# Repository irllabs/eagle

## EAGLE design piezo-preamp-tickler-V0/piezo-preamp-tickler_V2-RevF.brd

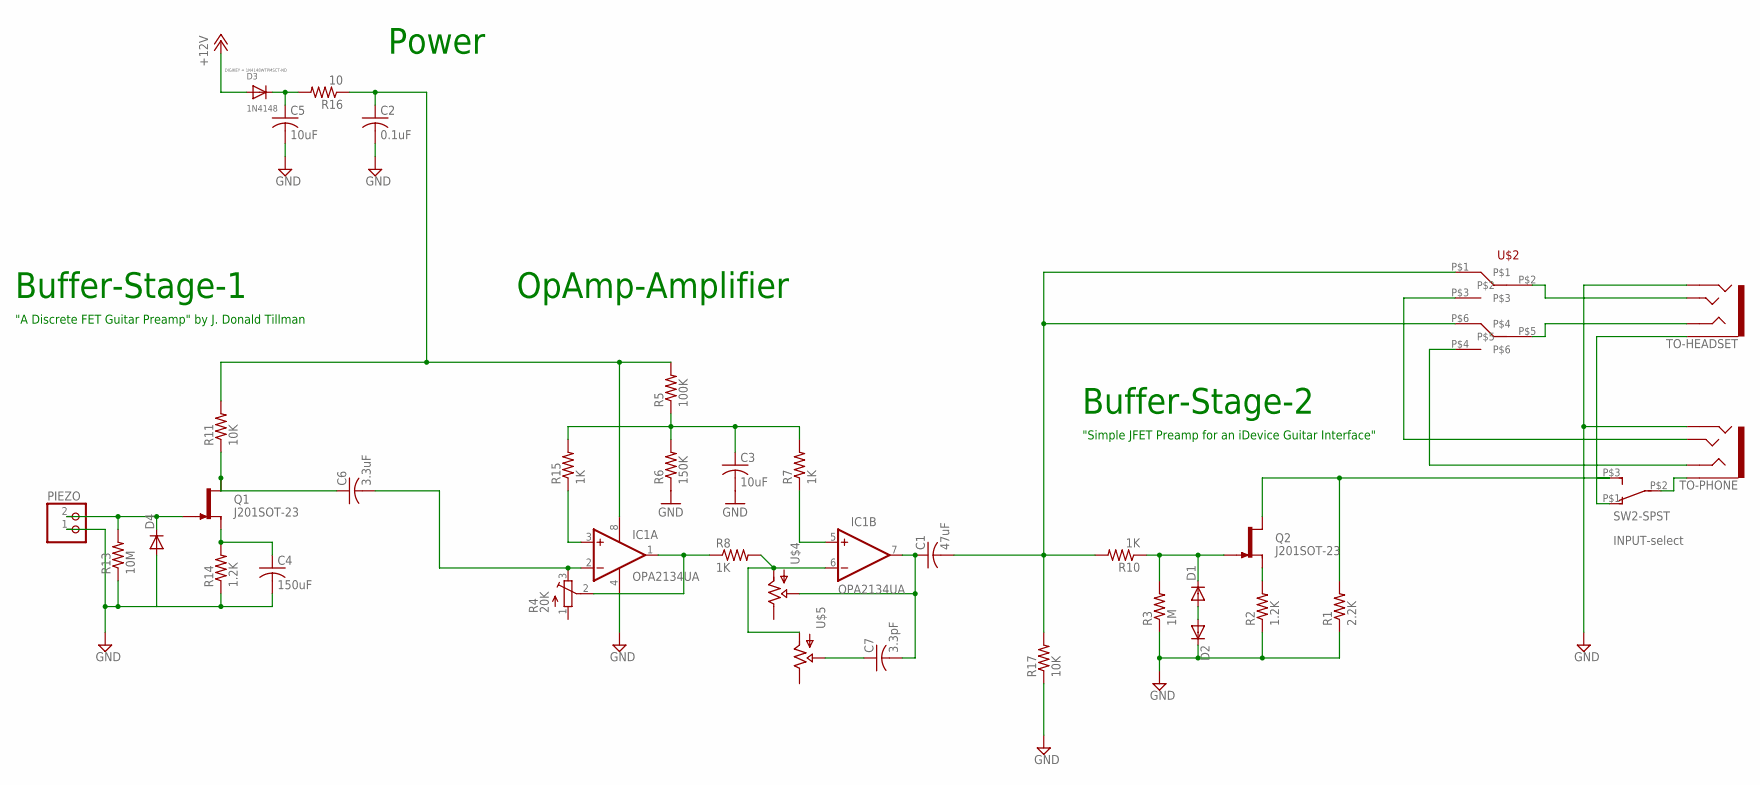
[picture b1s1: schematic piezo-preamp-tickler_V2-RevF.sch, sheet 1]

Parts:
C1: 47uF; CT7343
C2: 0.1uF; C0805K
C3, C5: 10uF; C0805K
C4: 150uF; CT7343
C6: 3.3uF; CT7343
C7: 3.3pF; C0805K
D1, D2, D4: DIODE-SOD123; SOD123
D3: 1N4148; SOD-123; DIGIKEY 1N4148WTPMSCT-ND
IC1: OPA2134UA; SO08
PIEZO: JST_2PIN-THM; JST-PH-2-THM
Q1, Q2: J201SOT-23; SOT23-3
R1: 2.2K; R0603
R2, R14: 1.2K; R0603
R3: 1M; R0603
R4: 20K; TC33X
R5: 100K; R0603
R6: 150K; R0603
R7, R8, R10, R15: 1K; R0603
R11, R17: 10K; R0603
R13: 10M; R0603
R16: 10; R0603
SW2-SPST: INPUT-select; SWITCH_SPDT_CL-SB-12B
TO-HEADSET: AUDIO-JACK3LGPADS; AUDIO-JACK-TRRS-SMD
TO-PHONE: AUDIO-JACK3LGPADS; AUDIO-JACK-TRRS-SMD
U$2: SWITCH_DPDT; SWITCH_DPDT_CL-SB-12B
U$4, U$5: POTTHUMBPOT14MM; THUMBPOT10MM

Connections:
+12V: D3.A; also elsewhere on the board
GND: C2.2, C3.2, C4.- (2), C5.2, D2.C, D4.A, IC1.4 (V-), PIEZO.1 (2), R1.1, R2.1, R3.1, R6.1, R13.1, R14.1, R17.1, TO-HEADSET.RING2, TO-PHONE.RING2; also elsewhere on the board
unnamed: D1.A, D2.A
unnamed: D4.C, PIEZO.2 (1), Q1.3 (G), R13.2
unnamed: Q2.2 (S), R2.2
unnamed: IC1.5 (+IN), R7.1
unnamed: C1.+ (1), C7.2, IC1.7 (OUT), U$4.P$2 (WIPER)
unnamed: IC1.6 (-IN), R8.2, U$4.P$1 (IN), U$5.P$1 (IN)
unnamed: C6.+ (1), Q1.1 (D), R11.1
unnamed: D1.C, Q2.3 (G), R3.2, R10.1
unnamed: C1.- (2), R10.2, R17.2, U$2.P$1, U$2.P$6
unnamed: SW2-SPST.P$1 (1), TO-HEADSET.EARTH
unnamed: TO-HEADSET.TIP, U$2.P$2
unnamed: C4.+ (1), Q1.2 (S), R14.2
unnamed: TO-HEADSET.RING1, U$2.P$5
unnamed: C5.1, D3.C, R16.2
unnamed: SW2-SPST.P$2 (2), TO-PHONE.EARTH
unnamed: IC1.3 (+IN), R15.1
unnamed: C3.1, R5.1, R6.2, R7.2, R15.2
unnamed: IC1.1 (OUT), R4.2 (S), R8.1
unnamed: C2.1, IC1.8 (V+), R5.2, R11.2, R16.1
unnamed: TO-PHONE.RING1, U$2.P$4
unnamed: TO-PHONE.TIP, U$2.P$3
unnamed: C6.- (2), IC1.2 (-IN), R4.3 (E)
unnamed: C7.1, U$5.P$2 (WIPER)
SELECT: Q2.1 (D), R1.2, SW2-SPST.P$3 (3)

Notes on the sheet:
Buffer-Stage-1
OpAmp-Amplifier
Buffer-Stage-2
"A Discrete FET Guitar Preamp" by J. Donald Tillman
"Simple JFET Preamp for an iDevice Guitar Interface"
Power

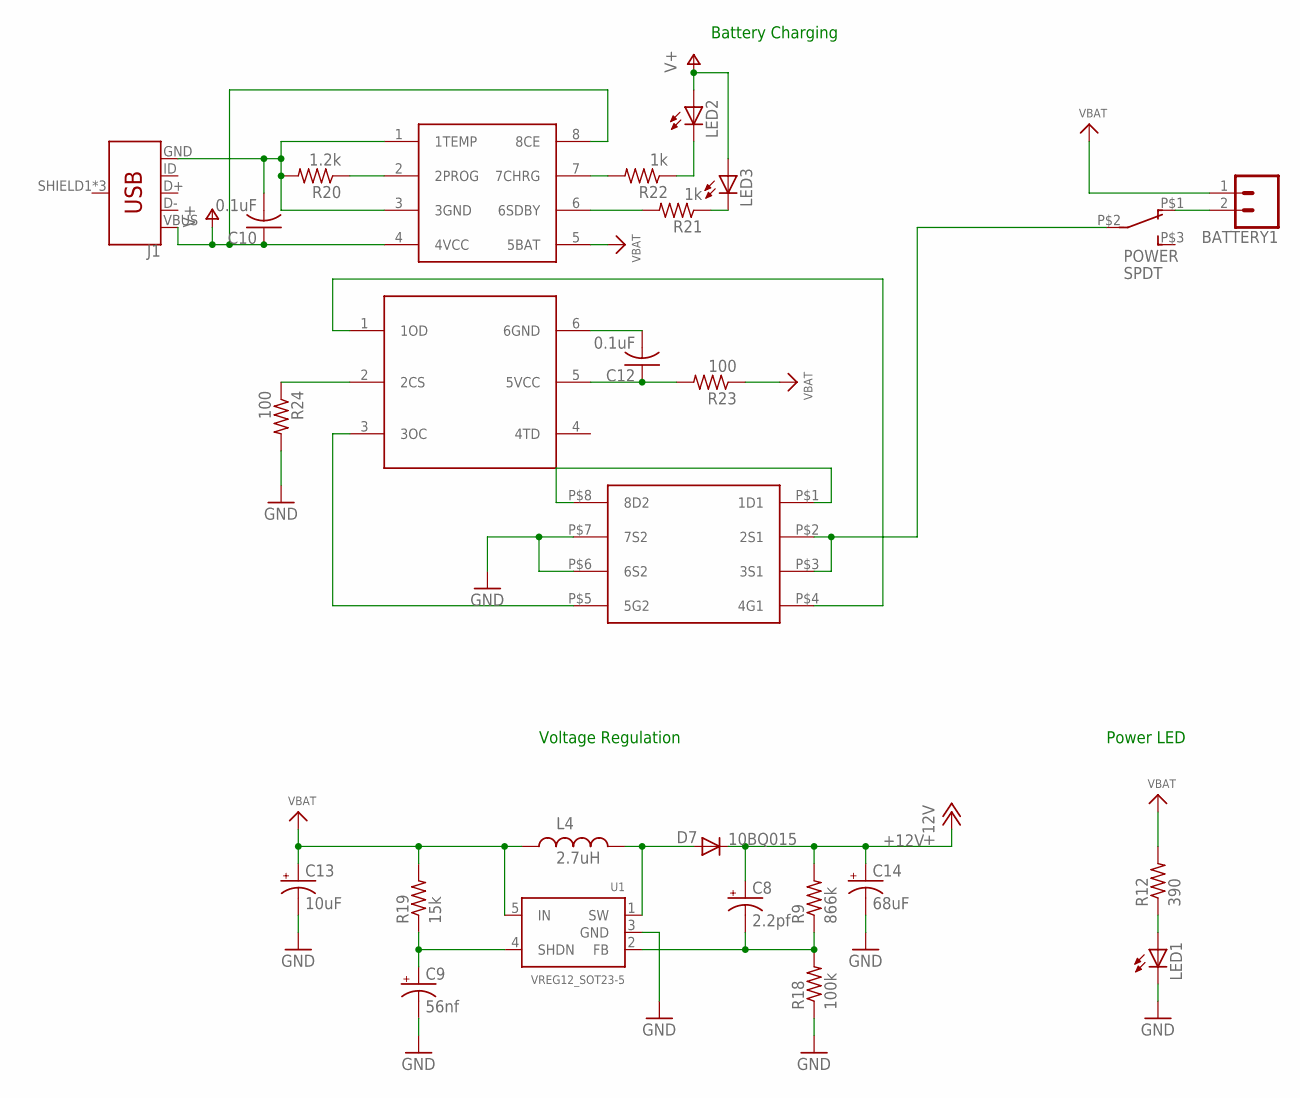
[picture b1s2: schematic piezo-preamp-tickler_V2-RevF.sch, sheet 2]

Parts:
BATTERY1: CONN_02LOCK; 1X02_LOCK
C8: 2.2pf; EIA3216
C9: 56nf; EIA3528
C10, C12: 0.1uF; C0805K
C13: 10uF; EIA3216
C14: 68uF; EIA3528
D7: 10BQ015; SMA-DIODE
J1: USB_MICRO-BREDUCED_PASTE; USB-B-MICRO-SMD_RED_PASTE
L4: 2.7uH; CR54
LED1, LED2, LED3: LED3MM
POWER: SPDT; SWITCH_SPDT_CL-SB-12B
R9: 866k; R0603
R12: 390; R0805
R18: 100k; R0603
R19: 15k; R0603
R20: 1.2k; R0603
R21, R22: 1k; R0603
R23, R24: 100; R0603
U1: VREG12_SOT23-5; SOT23-5
U$1: TP4056-CHIP; SO08
U$7: DW01A; SOT23-6
U$9: F8205A

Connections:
+12V: C8.A (+), C14.A (+), D7.C, R9.2; also elsewhere on the board
GND: C9.C (-), C13.C (-), C14.C (-), LED1.K (C), R18.1, R24.2, U1.3 (GND), U$9.P$6 (6S2), U$9.P$7 (7S2); also elsewhere on the board
unnamed: LED1.A, R12.1
unnamed: POWER.P$2 (2), U$9.P$2 (2S1), U$9.P$3 (3S1)
unnamed: BATTERY1.2, POWER.P$1 (1)
unnamed: C9.A (+), R19.1, U1.4 (SHDN)
unnamed: C8.C (-), R9.1, R18.2, U1.2 (FB)
unnamed: D7.A, L4.P$2 (2), U1.1 (SW)
unnamed: C10.2, J1.GND, R20.2, U$1.1 (1TEMP), U$1.3 (3GND)
unnamed: U$7.1 (1OD), U$9.P$4 (4G1)
unnamed: R20.1, U$1.2 (2PROG)
unnamed: U$7.3 (3OC), U$9.P$5 (5G2)
unnamed: R22.2, U$1.7 (7CHRG)
unnamed: R21.2, U$1.6 (6SDBY)
unnamed: LED3.K (C), R21.1
unnamed: LED2.K (C), R22.1
unnamed: C12.1, R23.2, U$7.5 (5VCC)
unnamed: C12.2, U$7.6 (6GND)
unnamed: R24.1, U$7.2 (2CS)
unnamed: U$9.P$1 (1D1), U$9.P$8 (8D2)
V+: C10.1, J1.VBUS, LED2.A, LED3.A, U$1.4 (4VCC), U$1.8 (8CE)
VBAT: BATTERY1.1, C13.A (+), L4.P$1 (1), R12.2, R19.2, R23.1, U1.5 (IN), U$1.5 (5BAT)

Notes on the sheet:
Voltage Regulation
Battery Charging
Power LED

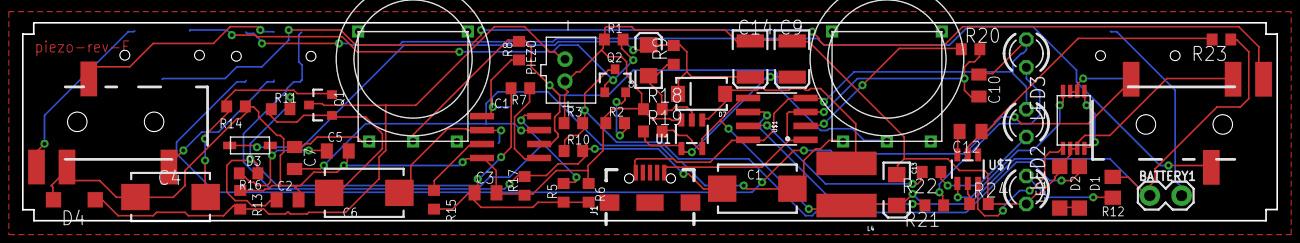
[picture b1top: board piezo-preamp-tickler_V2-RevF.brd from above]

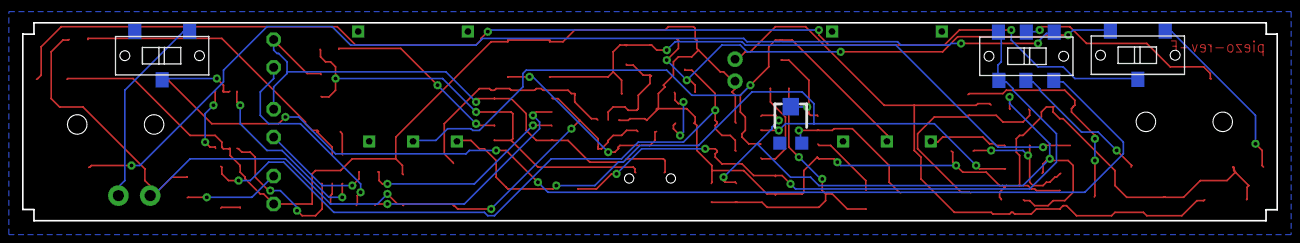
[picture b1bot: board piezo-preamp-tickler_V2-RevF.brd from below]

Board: 2 copper layers, 114.3 x 18.0 mm, 63 parts (4 on the bottom side), 46 nets.

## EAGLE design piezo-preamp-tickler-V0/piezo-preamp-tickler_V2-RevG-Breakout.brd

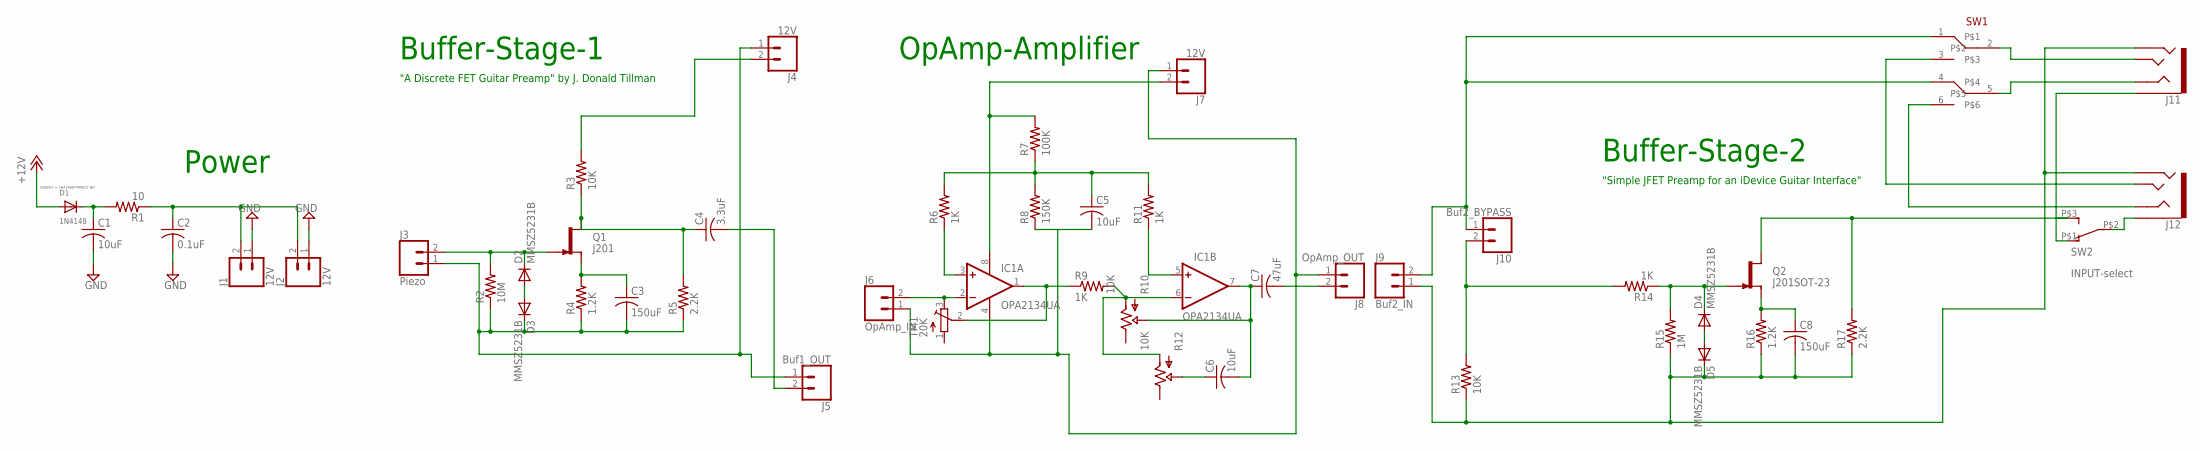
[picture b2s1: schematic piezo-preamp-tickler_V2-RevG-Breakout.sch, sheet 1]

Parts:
C1, C5, C6: 10uF; C0805K
C2: 0.1uF; C0805K
C3, C8: 150uF; CT7343
C4: 3.3uF; CT7343
C7: 47uF; CT7343
D1: 1N4148; SOD-123; DIGIKEY 1N4148WTPMSCT-ND
D2, D3, D4, D5: MMSZ5231B; SOD123
IC1: OPA2134UA; SO08
J1, J2, J4, J7: 12V; 1X02
J3: Piezo; 1X02
J5: Buf1_OUT; 1X02
J6: OpAmp_IN; 1X02
J8: OpAmp_OUT; 1X02
J9: Buf2_IN; 1X02
J10: Buf2_BYPASS; 1X02
J11, J12: AUDIO-JACK3LGPADS; AUDIO-JACK-TRRS-SMD
Q1: J201; SOT23-3
Q2: J201SOT-23; SOT23-3
R1: 10; R0805
R2: 10M; R0805
R3, R13: 10K; R0805
R4, R16: 1.2K; R0805
R5, R17: 2.2K; R0805
R6, R9, R11, R14: 1K; R0805
R7: 100K; R0805
R8: 150K; R0805
R10, R12: 10K; THUMBPOT14
R15: 1M; R0805
SW1: SWITCH_DPDT; SWITCH_DPDT_CL-SB-22B
SW2: INPUT-select; SWITCH_SPDT_CL-SB-12B
TM1: 20K; TC33X

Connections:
+12V: D1.A; also elsewhere on the board
GND: C1.2, C2.2, J1.1, J2.1; also elsewhere on the board
unnamed: D4.A, D5.A
unnamed: D2.C, J3.2, Q1.3 (G), R2.2
unnamed: C8.+ (1), Q2.2 (S), R16.2
unnamed: IC1.5 (+IN), R11.1
unnamed: C6.2, C7.+ (1), IC1.7 (OUT), R10.P$2 (WIPER)
unnamed: IC1.6 (-IN), R9.2, R10.P$1 (IN), R12.P$1 (IN)
unnamed: D2.A, D3.A
unnamed: C4.+ (1), Q1.1 (D), R3.1, R5.2
unnamed: D4.C, Q2.3 (G), R14.1, R15.2
unnamed: J9.2, J10.1, SW1.1, SW1.4
unnamed: J11.EARTH, SW2.P$1 (1)
unnamed: J11.TIP, SW1.2
unnamed: C3.+ (1), Q1.2 (S), R4.2
unnamed: J11.RING1, SW1.5
unnamed: C1.1, D1.C, R1.2
unnamed: J12.EARTH, SW2.P$2 (2)
unnamed: IC1.2 (-IN), J6.2, TM1.3 (E)
unnamed: C3.- (2), D3.C, J3.1, J4.1, J5.1, R2.1, R4.1, R5.1
unnamed: IC1.3 (+IN), R6.1
unnamed: C5.1, R6.2, R7.1, R8.2, R11.2
unnamed: IC1.1 (OUT), R9.1, TM1.2 (S)
unnamed: J4.2, R3.2
unnamed: J12.RING1, SW1.6
unnamed: J12.TIP, SW1.3
unnamed: C4.- (2), J5.2
unnamed: C6.1, R12.P$2 (WIPER)
unnamed: C7.- (2), J8.2
unnamed: IC1.8 (V+), J7.2, R7.2
unnamed: C2.1, J1.2, J2.2, R1.1
unnamed: C5.2, IC1.4 (V-), J6.1, J7.1, J8.1, R8.1
unnamed: C8.- (2), D5.C, J9.1, J11.RING2, J12.RING2, R13.1, R15.1, R16.1, R17.1
unnamed: J10.2, R13.2, R14.2
SELECT: Q2.1 (D), R17.2, SW2.P$3 (3)

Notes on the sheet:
Buffer-Stage-1
OpAmp-Amplifier
Buffer-Stage-2
"A Discrete FET Guitar Preamp" by J. Donald Tillman
"Simple JFET Preamp for an iDevice Guitar Interface"
Power

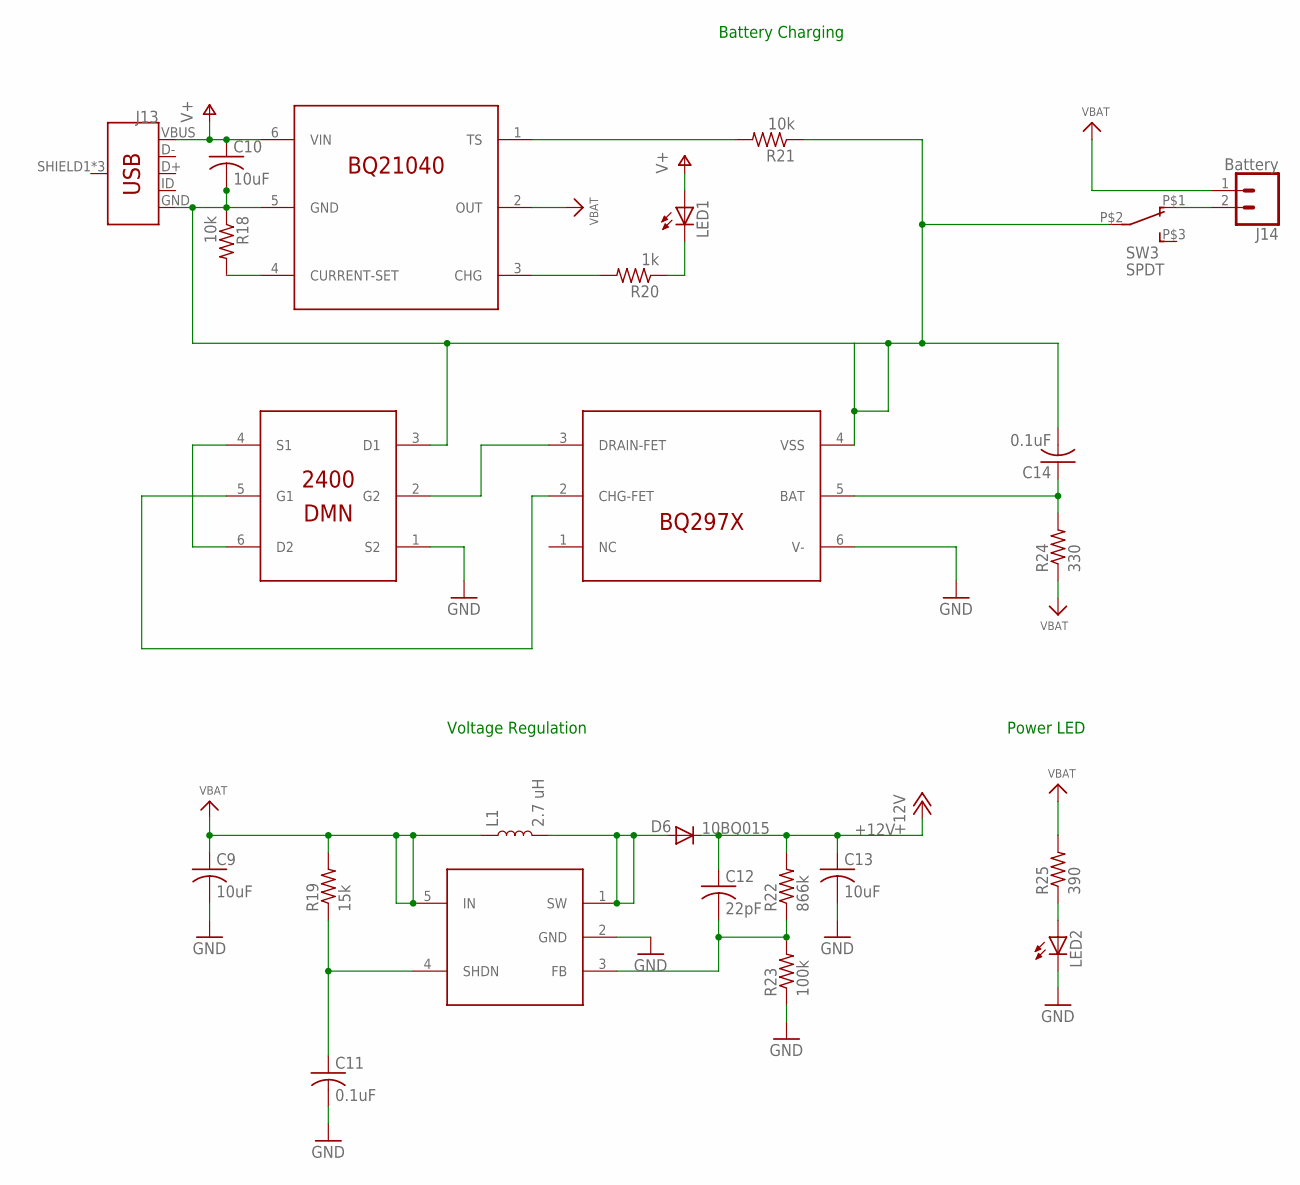
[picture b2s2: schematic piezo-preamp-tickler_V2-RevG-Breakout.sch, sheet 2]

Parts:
C9, C10, C13: 10uF; C0805K
C11, C14: 0.1uF; C0805K
C12: 22pF; C0805K
D6: 10BQ015; SMA-DIODE
J13: USB_MICRO-BREDUCED_PASTE; USB-B-MICRO-SMD_RED_PASTE
J14: Battery; 1X02_LOCK
L1: 2.7 uH; CR54
LED1, LED2: LED3MM
Q3: DMN2400; SOT-563
Q4: BQ21040; SOT23-6
Q5: SC4503; SOT23-5
Q6: BQ297X; WSON-6
R18, R21: 10k; R0805
R19: 15k; R0805
R20: 1k; R0805
R22: 866k; R0805
R23: 100k; R0805
R24: 330; R0805
R25: 390; R0805
SW3: SPDT; SWITCH_SPDT_CL-SB-12B

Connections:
+12V: C12.1, C13.1, D6.C, R22.2; also elsewhere on the board
GND: C9.2, C11.2, C13.2, LED2.K (C), Q3.1 (S2), Q5.2 (GND), Q6.6 (V-), R23.1; also elsewhere on the board
GND1: C10.2, C14.2, J13.GND, Q3.3 (D1), Q4.5 (GND), Q6.4 (VSS), R18.1, R21.1, SW3.P$2 (2)
unnamed: LED2.A, R25.1
unnamed: J14.2, SW3.P$1 (1)
unnamed: C11.1, Q5.4 (SHDN), R19.1
unnamed: C12.2, Q5.3 (FB), R22.1, R23.2
unnamed: D6.A, L1.P$2 (2), Q5.1 (SW)
unnamed: Q4.3 (CHG), R20.2
unnamed: C14.1, Q6.5 (BAT), R24.2
unnamed: Q4.1 (TS), R21.2
unnamed: Q3.4 (S1), Q3.6 (D2)
unnamed: Q4.4 (CURRENT-SET), R18.2
unnamed: Q3.5 (G1), Q6.2 (CHG-FET)
unnamed: LED1.K (C), R20.1
unnamed: Q3.2 (G2), Q6.3 (DRAIN-FET)
V+: C10.1, J13.VBUS, LED1.A, Q4.6 (VIN)
VBAT: C9.1, J14.1, L1.P$1 (1), Q4.2 (OUT), Q5.5 (IN), R19.2, R24.1, R25.2

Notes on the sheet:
Voltage Regulation
Battery Charging
Power LED

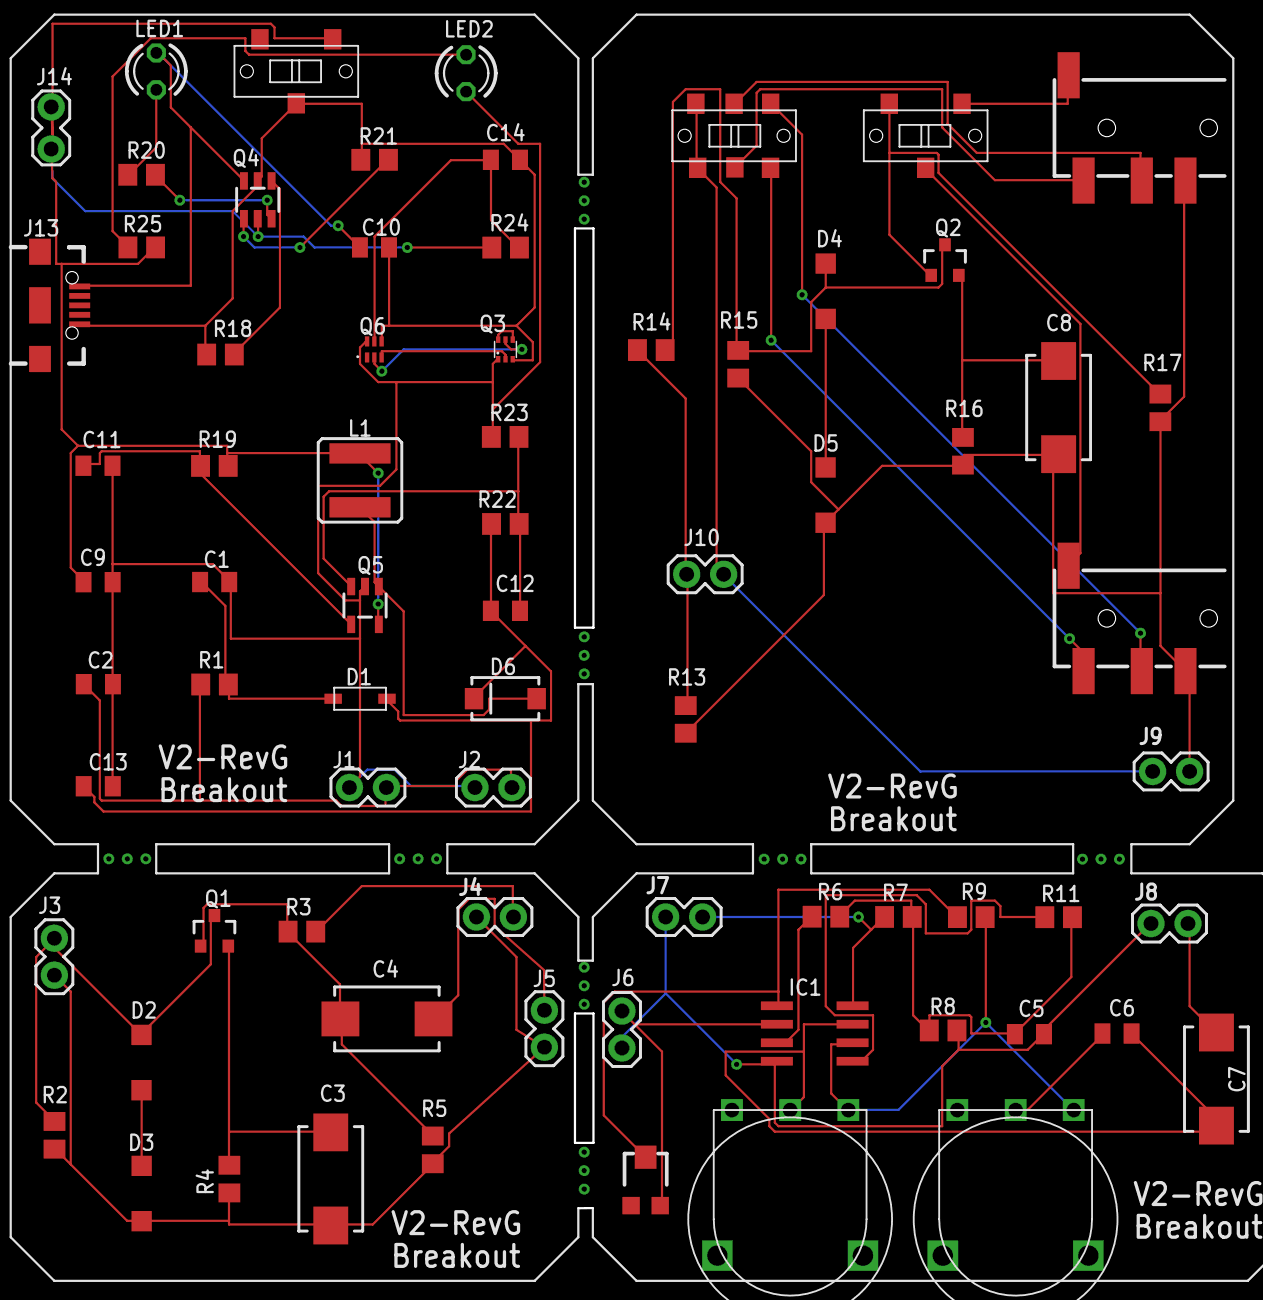
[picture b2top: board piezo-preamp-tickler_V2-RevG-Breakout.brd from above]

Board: 2 copper layers, 73 parts (0 on the bottom side), 51 nets.

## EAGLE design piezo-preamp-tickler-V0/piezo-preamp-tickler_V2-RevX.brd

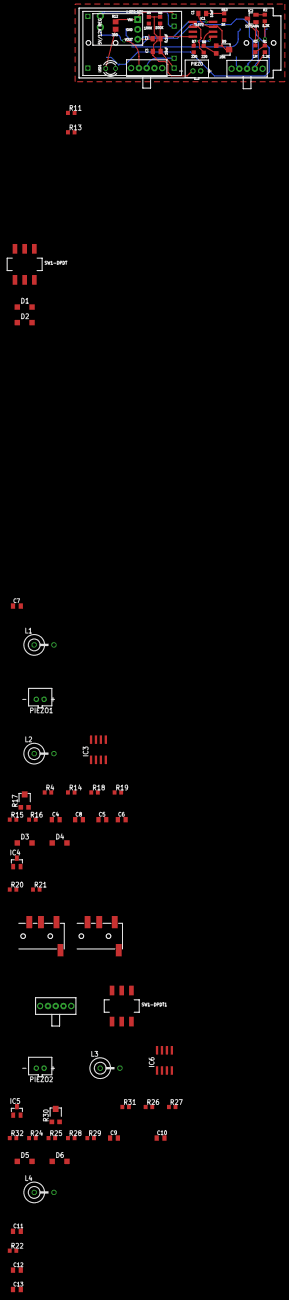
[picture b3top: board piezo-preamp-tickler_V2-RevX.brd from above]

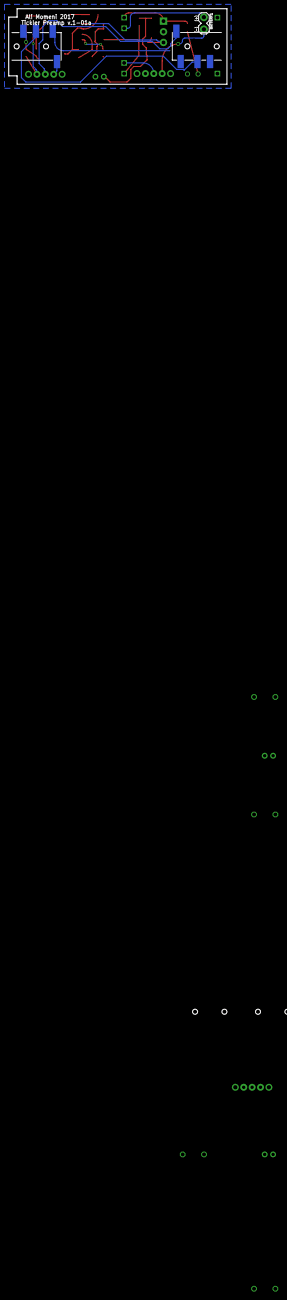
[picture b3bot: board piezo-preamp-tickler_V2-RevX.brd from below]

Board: 2 copper layers, 52.0 x 18.0 mm, 76 parts (3 on the bottom side), 57 nets.

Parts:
BATTERY1: 1X02_LOCK
C1, C3, C5, C6, C10, C12: 10uF; C0805K
C2, C4, C7, C8, C9, C11: 0.1uF; C0805K
C13: 100uF; C0805K
D1, D2, D3, D4, D6: SOD123
D5: BAT45S; SOD123
IC1, IC6: TL072; SO08
IC2, IC5: SST5484; SOT23
IC3: OPA1612; SO08
IC4: J201; SOT23
J_REG_12V: POLOLU_VOLTAGE_REGULATORS_3PIN; POLOLU_5V-12V_STEPUP_U3V12F5-U3V12F12
L1, L2, L3, L4: 100uH; LBC-SE
LED1: LED3MM
PIEZO, PIEZO1, PIEZO2: JST-PH-2-THM
POWER: SPDT; SWITCH_SPDT-TE-CONNECT
R1, R21, R22, R27: 2.2K; R0603
R2, R20, R26: 1.2K; R0603
R3, R28: 1M; R0603
R4, R5, R6, R11, R14, R18, R31: 100K; R0603
R7, R8, R15, R16, R24, R25: 220; R0603
R9, R17, R30: 20K; TC33X
R10, R29: 1K; R0603
R12: 390; R0805
R13, R19, R32: 10M; R0603
SW1-DPDT, SW1-DPDT1: OUTPUT-select; DPDT_SMT_JS202011SCQN
SW2-SPST, SW2-SPST1: INPUT-select; SWITCH_SPDT-TE-CONNECT
TO-HEADSET, TO-HEADSET1: AUDIO-JACK3LGPADS; AUDIO-JACK-TRRS-SMD
TO-PHONE, TO-PHONE1: AUDIO-JACK3LGPADS; AUDIO-JACK-TRRS-SMD
USB-LIPO-CHARGER: TP4056-MODULE; TP4056-LITHIUM-PROTECTED-MODULE

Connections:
+12V: D5.C, J_REG_12V.VOUT, L1.1, L2.1, L3.1, R22.2
-12V: D6.A, L4.1
GND: C2.2, C3.2, C4.2, C6.2, C7.2, C8.2, C9.2, C11.1, C12.2, D2.C, D4.C, IC1.4, IC3.4, J_REG_12V.GND, LED1.K, PIEZO.1, PIEZO1.1, PIEZO2.1, R1.1, R2.1, R3.1, R6.1, R14.1, R20.1, R21.1, R24.2, R26.1, R27.1, R28.1, R32.1, TO-HEADSET.RING2, TO-HEADSET1.RING2, TO-PHONE.RING2, TO-PHONE1.RING2, USB-LIPO-CHARGER.OUT-
unnamed: C13.1, IC3.1, IC3.2
unnamed: PIEZO.2, R11.1
unnamed: IC2.2, R2.2
unnamed: IC1.5, R7.1
unnamed: C2.1, IC1.8, L1.2, R5.2
unnamed: IC1.6, R8.2, R9.3
unnamed: D1.A, D2.A
unnamed: D1.C, IC1.3, R11.2, R13.2
unnamed: IC2.3, R3.2, R10.1
unnamed: C1.2, R10.2, SW1-DPDT.P$3, SW1-DPDT.P$4
unnamed: SW2-SPST.1, TO-HEADSET.EARTH
unnamed: SW1-DPDT.P$5, TO-HEADSET.TIP
unnamed: IC1.1, IC1.2, R8.1
unnamed: SW1-DPDT.P$2, TO-HEADSET.RING1
unnamed: IC3.5, R15.1
unnamed: SW2-SPST.2, TO-PHONE.EARTH
unnamed: LED1.A, R12.1
unnamed: BATTERY1.1, USB-LIPO-CHARGER.B+
unnamed: POWER.2, USB-LIPO-CHARGER.B-
unnamed: BATTERY1.2, POWER.1
unnamed: IC3.6, R16.2, R17.3
unnamed: PIEZO1.2, R18.1
unnamed: IC3.3, IC4.1, R21.2, R22.1
unnamed: SW1-DPDT.P$1, TO-PHONE.RING1
unnamed: SW1-DPDT.P$6, TO-PHONE.TIP
unnamed: C3.1, C7.1, R5.1, R6.2, R7.2, R13.1
unnamed: D3.A, D4.A
unnamed: IC5.2, R26.2
unnamed: C5.1, IC3.7, R17.1, R17.2
unnamed: C4.1, IC3.8, L2.2, R4.2
unnamed: C12.1, IC4.2, R20.2
unnamed: IC6.1, IC6.2, R25.1
unnamed: C6.1, C8.1, R4.1, R14.2, R15.2, R19.1
unnamed: D3.C, IC4.3, R18.2, R19.2
unnamed: IC6.5, R24.1
unnamed: IC6.6, R25.2, R30.3
unnamed: IC5.3, R28.2, R29.1
unnamed: C1.1, IC1.7, R9.1, R9.2
unnamed: C10.2, R29.2, SW1-DPDT1.P$3, SW1-DPDT1.P$4
unnamed: SW2-SPST1.1, TO-HEADSET1.EARTH
unnamed: SW1-DPDT1.P$5, TO-HEADSET1.TIP
unnamed: SW1-DPDT1.P$2, TO-HEADSET1.RING1
unnamed: SW2-SPST1.2, TO-PHONE1.EARTH
unnamed: PIEZO2.2, R31.1
unnamed: SW1-DPDT1.P$1, TO-PHONE1.RING1
unnamed: SW1-DPDT1.P$6, TO-PHONE1.TIP
unnamed: C11.2, IC6.4, L4.2
unnamed: C13.2, R16.1
unnamed: C10.1, IC6.7, R30.1, R30.2
unnamed: C9.1, IC6.8, L3.2
unnamed: D5.A, D6.C, IC6.3, R31.2, R32.2
SELECT: IC2.1, R1.2, SW2-SPST.3
SELECT1: IC5.1, R27.2, SW2-SPST1.3
VBAT: J_REG_12V.VIN, R12.2, USB-LIPO-CHARGER.OUT+

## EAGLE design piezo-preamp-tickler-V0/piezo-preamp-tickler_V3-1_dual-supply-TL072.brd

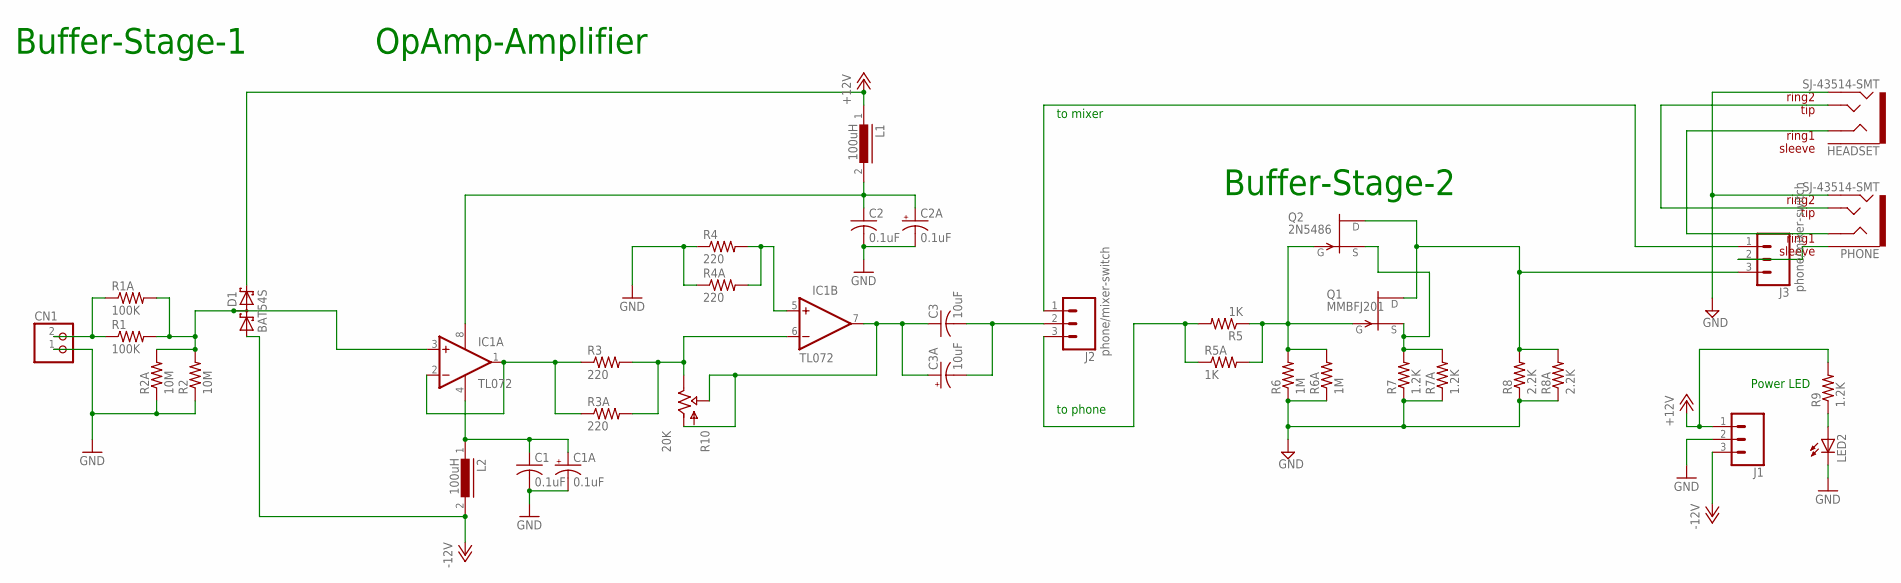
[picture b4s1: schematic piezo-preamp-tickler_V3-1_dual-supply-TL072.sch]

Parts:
C1, C2: 0.1uF; C0805K
C1A, C2A: 0.1uF; E2,5-6E
C3: 10uF; C1206
C3A: 10uF; E2,5-6E
CN1: JST_2PIN-THM; JST-PH-2-THM
D1: BAT54S; SOT23
HEADSET: SJ-43514-SMT; TRRS_SJ-43514-SMT-TR
IC1: TL072; SO08
J1: CONN_03LOCK; 1X03_LOCK
J2, J3: phone/mixer-switch; 1X03_LOCK
L1, L2: 100uH; LBC-SE
LED2: LED3MM
PHONE: SJ-43514-SMT; TRRS_SJ-43514-SMT-TR
Q1: MMBFJ201; SOT23
Q2: 2N5486; TO92-
R1: 100K; R0603
R1A: 100K; 0204V
R2: 10M; R0603
R2A: 10M; 0204V
R3, R4: 220; R0603
R3A, R4A: 220; 0204V
R5: 1K; R0603
R5A: 1K; 0204V
R6: 1M; R0603
R6A: 1M; 0204V
R7: 1.2K; R0603
R7A, R9: 1.2K; 0204V
R8: 2.2K; R0603
R8A: 2.2K; 0204V
R10: 20K; TRIMPOT-MULTI

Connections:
+12V: D1.2 (C2), J1.1, L1.1, R9.2
-12V: D1.1 (A1), J1.3, L2.2
GND: C1.2, C1A.-, C2.2, C2A.-, CN1.1 (2), HEADSET.RING2, J1.2, LED2.K (C), PHONE.RING2, R2.1, R2A.1, R4.1, R4A.1, R6.1, R6A.1, R7.1, R7A.1, R8.1, R8A.1
unnamed: IC1.1 (OUT), IC1.2 (-IN), R3.1, R3A.1
unnamed: J2.3, R5.2, R5A.1
unnamed: C1.1, C1A.+, IC1.4 (V-), L2.1
unnamed: LED2.A, R9.1
unnamed: IC1.5 (+IN), R4.2, R4A.2
unnamed: IC1.6 (-IN), R3.2, R3A.2, R10.P$1 (OUT), R10.P$3 (OUT), R10.P$4 (OUT), R10.P$6 (OUT), R10.P$9 (OUT)
unnamed: C3.2, C3A.-, J2.2
unnamed: CN1.2 (1), R1.1, R1A.1
unnamed: Q1.2 (S), Q2.2 (S), R7.2, R7A.2
unnamed: C3.1, C3A.+, IC1.7 (OUT), R10.P$10 (WIPER), R10.P$12 (WIPER), R10.P$13 (WIPER), R10.P$15 (WIPER), R10.P$16 (WIPER), R10.P$18 (WIPER), R10.P$20 (IN), R10.P$21 (IN), R10.P$22 (IN), R10.P$24 (IN), R10.P$27 (IN)
unnamed: C2.1, C2A.+, IC1.8 (V+), L1.2
unnamed: D1.3 (C1A2), IC1.3 (+IN), R1.2, R1A.2, R2.2, R2A.2
unnamed: Q1.3 (G), Q2.1 (G), R5.1, R5A.2, R6.2, R6A.2
unnamed: J2.1, J3.1
unnamed: HEADSET.TIP, PHONE.TIP
unnamed: HEADSET.RING1, PHONE.RING1
unnamed: J3.2, PHONE.EARTH
SELECT1: J3.3, Q1.1 (D), Q2.3 (D), R8.2, R8A.2

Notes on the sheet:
Buffer-Stage-1
OpAmp-Amplifier
Buffer-Stage-2
to mixer
to phone
Power LED

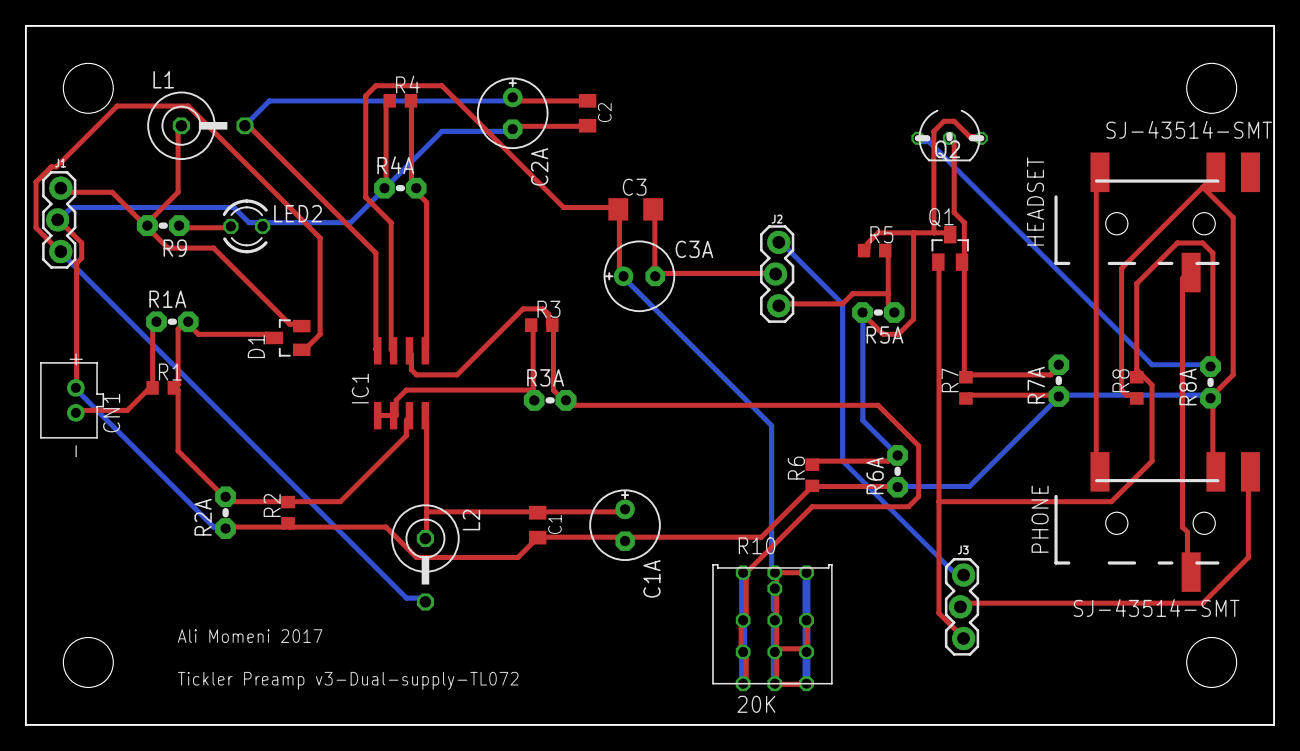
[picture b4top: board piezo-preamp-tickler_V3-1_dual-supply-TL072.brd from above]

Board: 2 copper layers, 100.0 x 56.0 mm, 37 parts (0 on the bottom side), 21 nets.

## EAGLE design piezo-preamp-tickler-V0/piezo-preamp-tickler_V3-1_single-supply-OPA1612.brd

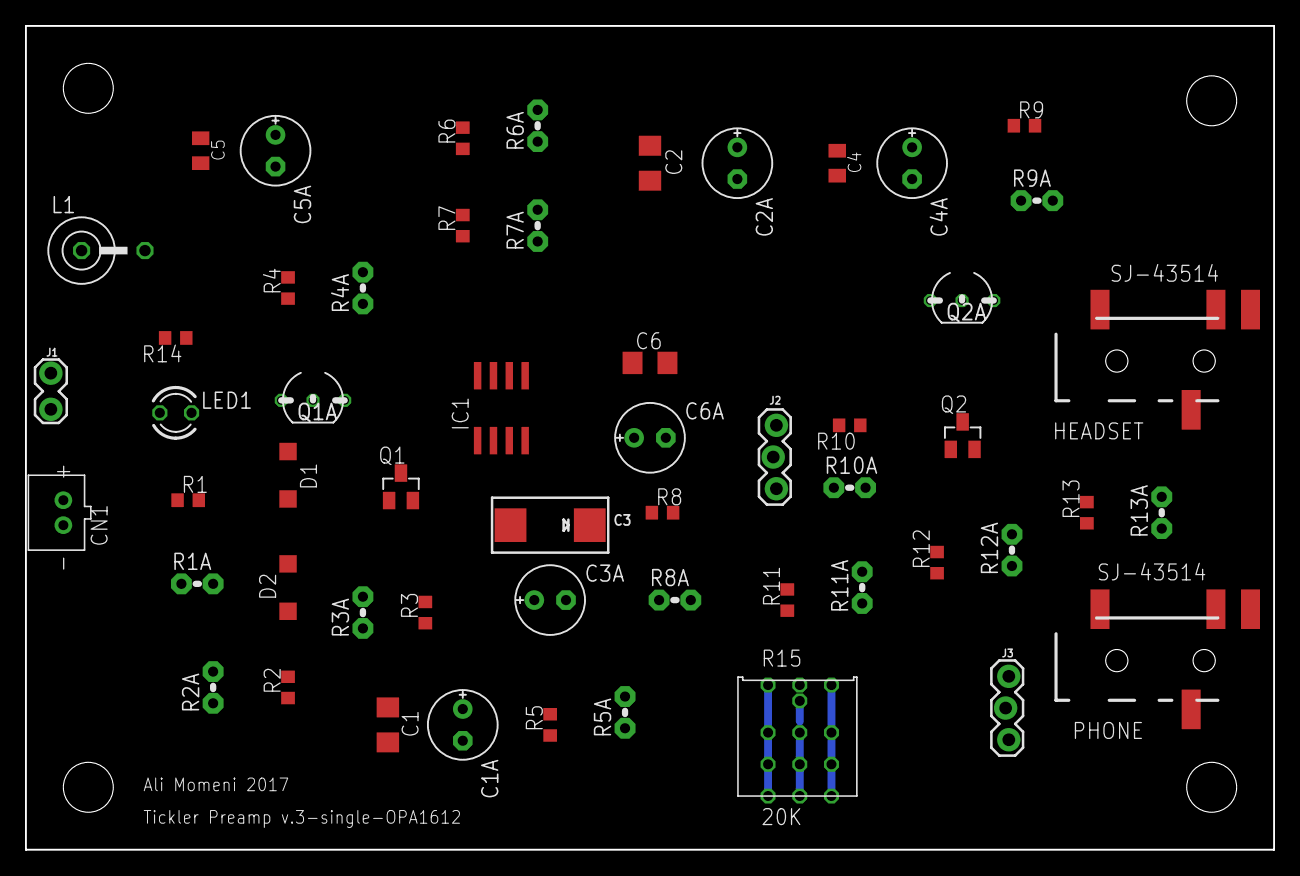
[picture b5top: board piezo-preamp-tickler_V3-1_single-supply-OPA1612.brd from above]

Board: 2 copper layers, 100.0 x 66.0 mm, 55 parts (0 on the bottom side), 24 nets, no tracks yet.

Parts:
C1, C2, C6: 10uF; C1206
C1A, C2A, C6A: 10uF; E2,5-6E
C3: mnove; EIA7343-31/D-R
C3A: 100uF; E2,5-6E
C4, C5: 0.1uF; C0805K
C4A, C5A: 0.1uF; E2,5-6E
CN1: JST-PH-2-THM
D1, D2: 1N4148W; SOD123
HEADSET: SJ-43514; TRRS_SJ-43514-SMT-TR
IC1: OPA1612; SO08
J1: 1X02_LOCK
J2, J3: phone/mixer-switch; 1X03_LOCK
L1: 100uH; LBC-SE
LED1: LED3MM
PHONE: SJ-43514; TRRS_SJ-43514-SMT-TR
Q1: J201; SOT23
Q1A, Q2A: 2N5486; TO92-
Q2: MMBFJ201; SOT23
R1, R6, R7: 100K; R0603
R1A, R6A, R7A: 100K; 0204V
R2: 10M; R0603
R2A: 10M; 0204V
R3, R12, R14: 1.2K; R0603
R3A, R12A: 1.2K; 0204V
R4, R5, R13: 2.2K; R0603
R4A, R5A, R13A: 2.2K; 0204V
R8, R9: 220; R0603
R8A, R9A: 220; 0204V
R10: 1K; R0603
R10A: 1K; 0204V
R11: 1M; R0603
R11A: 1M; 0204V
R15: 20K; TRIMPOT-MULTI

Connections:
+12V: J1.1, L1.1, R4.2, R4A.2, R14.2
DRAINE1: IC1.3, Q1.1, Q1A.3, R4.1, R4A.1, R5.2, R5A.2
GATE1: D1.C, Q1.3, Q1A.1, R1.2, R1A.2, R2.2, R2A.2
GATE2: Q2.3, Q2A.1, R10.1, R10A.2, R11.2, R11A.2
GND: C1.2, C1A.-, C2.2, C2A.-, C4.2, C4A.-, C5.2, C5A.-, CN1.1, D2.C, HEADSET.RING2, IC1.4, J1.2, LED1.K, PHONE.RING2, R3.1, R3A.1, R5.1, R5A.1, R7.1, R7A.1, R11.1, R11A.1, R12.1, R12A.1, R13.1, R13A.1
unnamed: C3.+, C3A.+, IC1.1, IC1.2
unnamed: LED1.A, R14.1
unnamed: J2.3, R10.2, R10A.1
unnamed: D1.A, D2.A
unnamed: IC1.5, R9.2, R9A.2
unnamed: IC1.6, R8.2, R8A.2, R15.P$1, R15.P$3, R15.P$4, R15.P$6, R15.P$9
unnamed: C6.2, C6A.-, J2.2
unnamed: CN1.2, R1.1, R1A.1
unnamed: C6.1, C6A.+, IC1.7, R15.P$10, R15.P$12, R15.P$13, R15.P$15, R15.P$16, R15.P$18
unnamed: C5.1, C5A.+, IC1.8, L1.2, R6.2, R6A.2
unnamed: C2.1, C2A.+, C4.1, C4A.+, R2.1, R2A.1, R6.1, R6A.1, R7.2, R7A.2, R9.1, R9A.1
unnamed: J2.1, J3.1
unnamed: HEADSET.TIP, PHONE.TIP
unnamed: HEADSET.RING1, PHONE.RING1
unnamed: J3.2, PHONE.EARTH
unnamed: C3.-, C3A.-, R8.1, R8A.1
NAME: J3.3, Q2.1, Q2A.3, R13.2, R13A.2
SOURCE: Q2.2, Q2A.2, R12.2, R12A.2
SOURCE1: C1.1, C1A.+, Q1.2, Q1A.2, R3.2, R3A.2

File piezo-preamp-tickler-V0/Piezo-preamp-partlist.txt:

Partlist

Exported from piezo-preamp-tickler_V3-2_single-supply-OPA1642.sch at 12/20/2017 9:03 PM

"EAGLE Version 8.5.1 Copyright (c) 1988-2017 Autodesk, Inc."

Assembly variant: 

Part       Value          Device                    Package               Library             Sheet

C2         10uF           C-USC1206                 C1206                 rcl                 1
C3         100uF          CAP_TANTALUMD/7343_REFLOW EIA7343-31/D-R        microbuilder        1
C4         0.1uF          C-USC0805K                C0805K                adafruit            1
C5         0.1uF          C-USC0805K                C0805K                adafruit            1
C6         10uF           C-USC1206                 C1206                 adafruit            1
CN1                       JST_2PIN-THM              JST-PH-2-THM          adafruit            1
D1         1N4148W        ZENER-DIOD                SOD123                CMU-ArtFab          1
D2         1N4148W        ZENER-DIOD                SOD123                CMU-ArtFab          1
HEADSET    SJ-43514       TRRS-3.5MMLGPADS          TRRS_SJ-43514-SMT-TR  CMU-ArtFab          1
IC1        OPA1612        OPA2134UA                 SO08                  linear              1
J1                        CONN_02LOCK               1X02_LOCK             SparkFun-Connectors 1
L1         100uH          L-USL3225P                L3225P                rcl                 1
LED1                      LED3MM                    LED3MM                led                 1
"MIXER-OUT  TRS-1/8""-3.5MM TRS-1/8""-3.5MM            TRS_SJ-3524-SMT       CMU-ArtFab          1"
PHONE      SJ-43514       TRRS-3.5MMLGPADS          TRRS_SJ-43514-SMT-TR  CMU-ArtFab          1
Q2         MMBFJ201       SST5484                   SOT23                 transistor-fet      1
R1         100K           R-US_R0603                R0603                 CMU-ArtFab          1
R2         10M            R-US_R0603                R0603                 CMU-ArtFab          1
R6         100K           R-US_R0603                R0603                 CMU-ArtFab          1
R7         100K           R-US_R0603                R0603                 CMU-ArtFab          1
R8         220            R-US_R0603                R0603                 CMU-ArtFab          1
R9         220            R-US_R0603                R0603                 CMU-ArtFab          1
R10        1K             R-US_R0603                R0603                 CMU-ArtFab          1
R11        1M             R-US_R0603                R0603                 CMU-ArtFab          1
R12        1.2K           R-US_R0603                R0603                 CMU-ArtFab          1
R13        2.2K           R-US_R0603                R0603                 CMU-ArtFab          1
R14        1.2K           R-US_R0603                R0603                 CMU-ArtFab          1
R15        20K            POTTRIMPOT-MULTI          TRIMPOT-MULTI         CMU-ArtFab          1
SW1-INPUT  SPDTCSS-1210B  SWITCH_SPDTCSS-1210B      SWITCH_SPDT_CSS-1210B CMU-ArtFab          1
SW1-OUTPUT SWITCH_DPDT    SWITCH_DPDT               SWITCH_DPDT_CL-SB-22B CMU-ArtFab          1

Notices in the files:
parts and their libraries:
SparkFun-Connectors: Licensing: Creative Commons ShareAlike 4.0 International - https://creativecommons.org/licenses/by-sa/4.0
microbuilder: This work is placed in the public domain, and may be freely used for commercial and non-commercial work with the following conditions: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
